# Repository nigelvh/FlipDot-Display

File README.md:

# FlipDot Display Driver
A driver for a flipdot display I found on eBay. Unfortunately I haven't found what the make/model of the display is. The design was based entirely on reverse engineering the connections.

## Hardware
These are the hardware design files. They're almost certainly terrible. Replicate this device at your own peril.

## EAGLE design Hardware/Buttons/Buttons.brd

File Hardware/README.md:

# Hardware Design
There are two custom PCBs I designed for this project, one simple one just supporting the input buttons, and the other that contains the actual logic and drivers for the flipdot panel.

The ESP32 handles all of the logic for the display, and feeds into the driver shift registers.

The drivers are MIC5841 (Low Side) and MIC5891 (High Side) devices, there's three pairs covering the 21 columns, and then two pairs covering the 14 rows. There are NAND gates on each set that provide an interlock preventing both the high side and low side drivers being active at the same time.

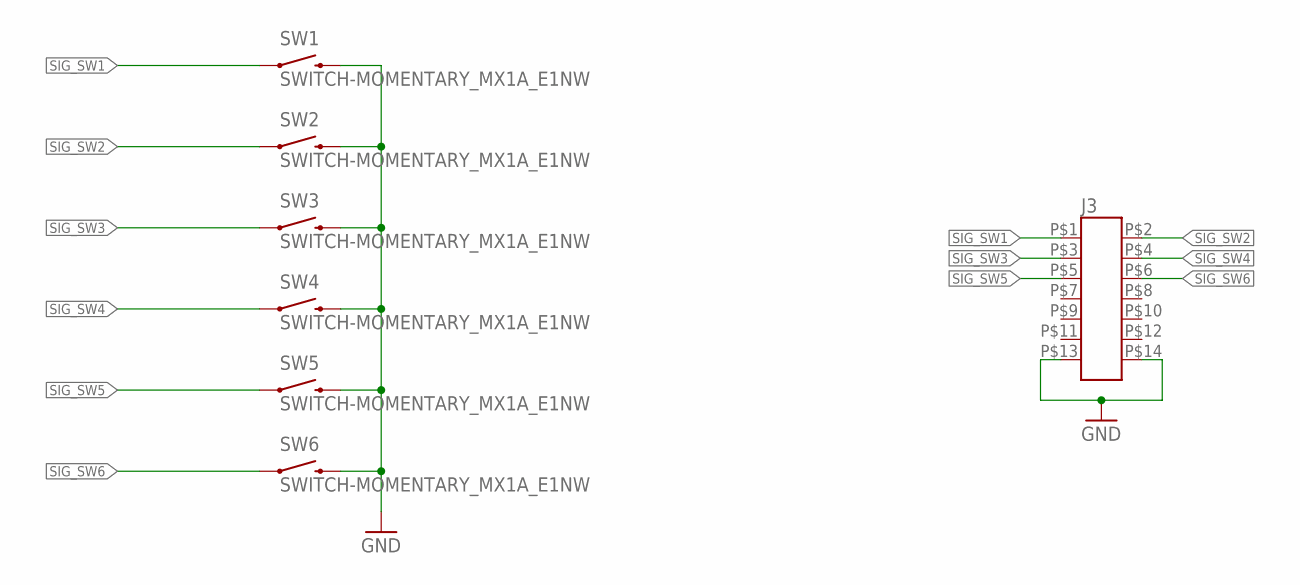
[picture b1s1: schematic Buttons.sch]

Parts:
J3: HEADER-2X7; 3M-3000SERIES-HEADER-RIGHTANGLE
SW1, SW2, SW3, SW4, SW5, SW6: SWITCH-MOMENTARY_MX1A_E1NW; CHERRY_MX1A_E1NW

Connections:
GND: J3.P$13 (13), J3.P$14 (14), SW1.P$2 (2), SW2.P$2 (2), SW3.P$2 (2), SW4.P$2 (2), SW5.P$2 (2), SW6.P$2 (2)
SIG_SW1: J3.P$1 (1), SW1.P$1 (1)
SIG_SW2: J3.P$2 (2), SW2.P$1 (1)
SIG_SW3: J3.P$3 (3), SW3.P$1 (1)
SIG_SW4: J3.P$4 (4), SW4.P$1 (1)
SIG_SW5: J3.P$5 (5), SW5.P$1 (1)
SIG_SW6: J3.P$6 (6), SW6.P$1 (1)

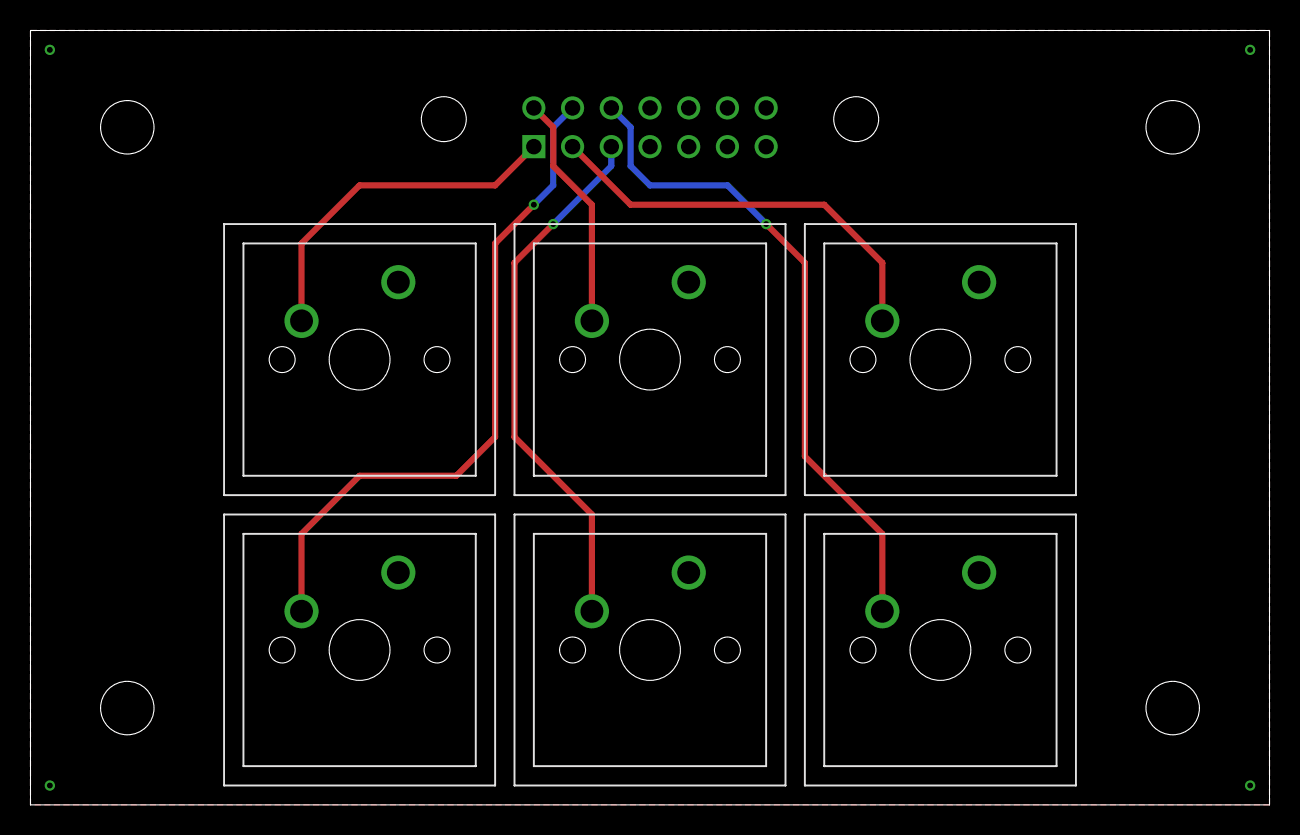
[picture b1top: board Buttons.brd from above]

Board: 2 copper layers, 81.3 x 50.8 mm, 7 parts (0 on the bottom side), 7 nets.

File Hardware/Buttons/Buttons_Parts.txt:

Partlist

Exported from Buttons.sch at 7/29/24 21:16

EAGLE Version 7.7.0 Copyright (c) 1988-2016 CadSoft

Assembly variant: 

Part     Value                      Device                     Package                         Library  Sheet

J3       HEADER-2X7                 HEADER-2X7                 3M-3000SERIES-HEADER-RIGHTANGLE Nigel    1
SW1      SWITCH-MOMENTARY_MX1A_E1NW SWITCH-MOMENTARY_MX1A_E1NW CHERRY_MX1A_E1NW                Nigel    1
SW2      SWITCH-MOMENTARY_MX1A_E1NW SWITCH-MOMENTARY_MX1A_E1NW CHERRY_MX1A_E1NW                Nigel    1
SW3      SWITCH-MOMENTARY_MX1A_E1NW SWITCH-MOMENTARY_MX1A_E1NW CHERRY_MX1A_E1NW                Nigel    1
SW4      SWITCH-MOMENTARY_MX1A_E1NW SWITCH-MOMENTARY_MX1A_E1NW CHERRY_MX1A_E1NW                Nigel    1
SW5      SWITCH-MOMENTARY_MX1A_E1NW SWITCH-MOMENTARY_MX1A_E1NW CHERRY_MX1A_E1NW                Nigel    1
SW6      SWITCH-MOMENTARY_MX1A_E1NW SWITCH-MOMENTARY_MX1A_E1NW CHERRY_MX1A_E1NW                Nigel    1

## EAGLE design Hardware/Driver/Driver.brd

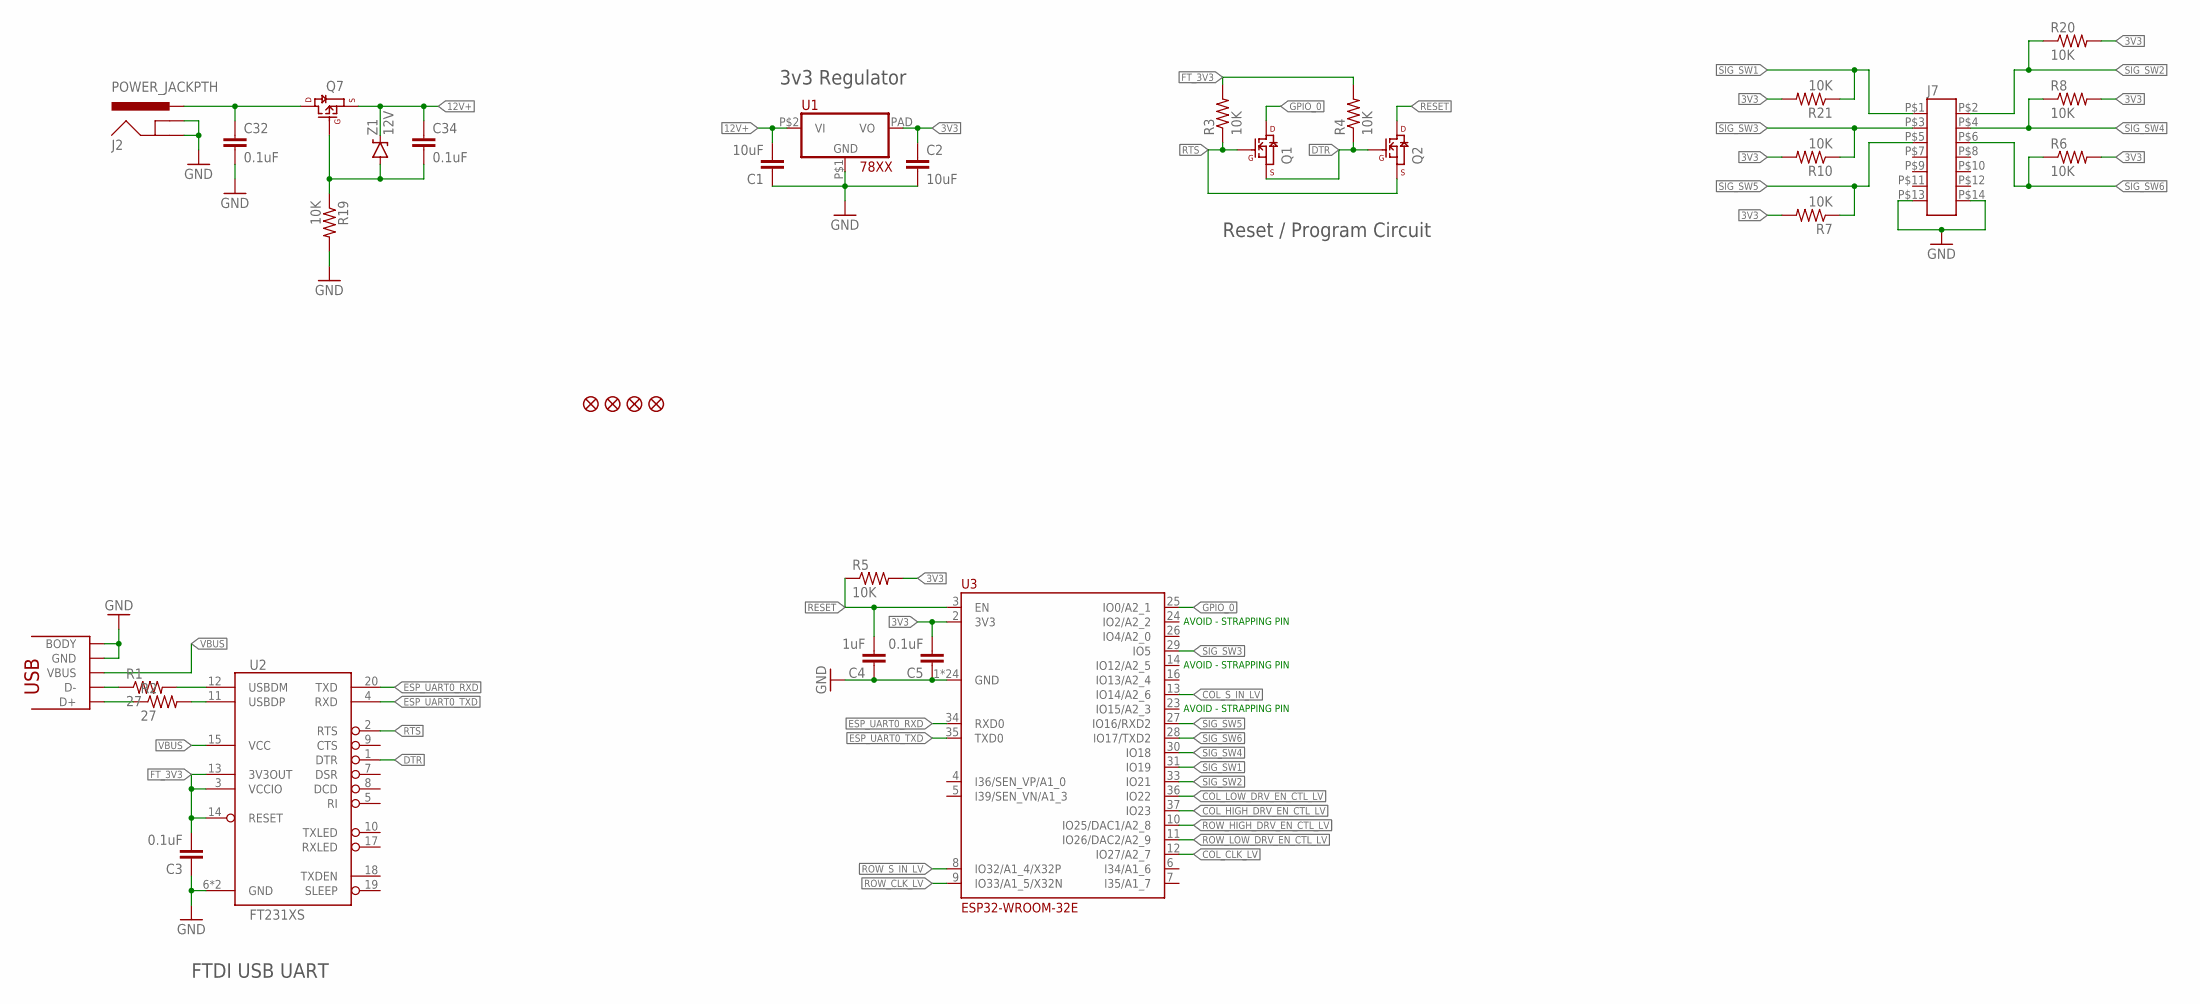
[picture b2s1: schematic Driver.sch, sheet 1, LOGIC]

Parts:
C1, C2: 10uF; 1206
C3, C5, C32, C34: 0.1uF; 0603-CAP
C4: 1uF; 0603-CAP
FID1, FID2, FID3, FID4: FIDUCIAL
J1: USB-MICROB; USB-MICROB-10118192
J2: POWER_JACKPTH; POWER_JACK_PTH
J7: HEADER-2X7; 3M-3000SERIES-HEADER-RIGHTANGLE
Q1, Q2: MOSFET_N_CHANNELFDV305N; SOT-23
Q7: MOSFET_P_CHANNELDMP4015SSS; SO08
R1, R2: 27; 0603-RES
R3, R4, R5, R6, R7, R8, R10, R19, R20, R21: 10K; 0603-RES
U1: 7805AZ1117_TO252; DPAK-3
U2: FT231XS; SSOP-20
U3: ESP32-WROOM-32E
Z1: 12V; SOT-23

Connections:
3V3: C2.1, C5.2, R5.2, R6.2, R7.2, R8.2, R10.2, R20.2, R21.2, U1.PAD (VO), U3.2 (3V3); also elsewhere on the board
12V+: C1.2, C34.1, Q7.1 (S), Q7.2 (S), Q7.3 (S), U1.P$2 (VI), Z1.3 (C); also elsewhere on the board
COL_CLK_LV: U3.12 (IO27/A2_7); also elsewhere on the board
COL_HIGH_DRV_EN_CTL_LV: U3.37 (IO23); also elsewhere on the board
COL_LOW_DRV_EN_CTL_LV: U3.36 (IO22); also elsewhere on the board
COL_S_IN_LV: U3.13 (IO14/A2_6); also elsewhere on the board
DTR: Q1.2 (S), Q2.1 (G), R4.1, U2.1 (DTR)
ESP_UART0_RXD: U2.20 (TXD), U3.34 (RXD0)
ESP_UART0_TXD: U2.4 (RXD), U3.35 (TXD0)
FT_3V3: C3.2, R3.2, R4.2, U2.3 (VCCIO), U2.13 (3V3OUT), U2.14 (RESET)
GND: C1.1, C2.2, C3.1, C4.1, C5.1, C32.2, J1.5 (GND), J1.BODY@1 (BODY), J1.BODY@2 (BODY), J1.BODY@3 (BODY), J1.BODY@4 (BODY), J1.BODY@5 (BODY), J1.BODY@6 (BODY), J2.GND, J2.GNDBREAK, J7.P$13 (13), J7.P$14 (14), R19.2, U1.P$1 (GND), U2.6 (GND), U2.16 (GND), U3.1 (GND), U3.15 (GND), U3.38 (GND), U3.P$1 (GND), U3.P$2 (GND), U3.P$3 (GND), U3.P$4 (GND), U3.P$5 (GND), U3.P$6 (GND), U3.P$7 (GND), U3.P$8 (GND), U3.P$9 (GND), U3.P$10 (GND), U3.P$11 (GND), U3.P$12 (GND), U3.PAD@1 (GND), U3.PAD@2 (GND), U3.PAD@3 (GND), U3.PAD@4 (GND), U3.PAD@5 (GND), U3.PAD@6 (GND), U3.PAD@7 (GND), U3.PAD@8 (GND), U3.PAD@9 (GND); also elsewhere on the board
GPIO_0: Q1.3 (D), U3.25 (IO0/A2_1)
unnamed: J1.2 (D-), R1.1
unnamed: J1.3 (D+), R2.1
unnamed: R2.2, U2.11 (USBDP)
unnamed: R1.2, U2.12 (USBDM)
unnamed: C32.1, J2.PWR, Q7.5 (D), Q7.6 (D), Q7.7 (D), Q7.8 (D)
unnamed: C34.2, Q7.4 (G), R19.1, Z1.1 (A)
RESET: C4.2, Q2.3 (D), R5.1, U3.3 (EN)
ROW_CLK_LV: U3.9 (IO33/A1_5/X32N); also elsewhere on the board
ROW_HIGH_DRV_EN_CTL_LV: U3.10 (IO25/DAC1/A2_8); also elsewhere on the board
ROW_LOW_DRV_EN_CTL_LV: U3.11 (IO26/DAC2/A2_9); also elsewhere on the board
ROW_S_IN_LV: U3.8 (IO32/A1_4/X32P); also elsewhere on the board
RTS: Q1.1 (G), Q2.2 (S), R3.1, U2.2 (RTS)
SIG_SW1: J7.P$1 (1), R21.1, U3.31 (IO19)
SIG_SW2: J7.P$2 (2), R20.1, U3.33 (IO21)
SIG_SW3: J7.P$3 (3), R10.1, U3.29 (IO5)
SIG_SW4: J7.P$4 (4), R8.1, U3.30 (IO18)
SIG_SW5: J7.P$5 (5), R7.1, U3.27 (IO16/RXD2)
SIG_SW6: J7.P$6 (6), R6.1, U3.28 (IO17/TXD2)
VBUS: J1.1 (VBUS), U2.15 (VCC)

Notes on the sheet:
FTDI USB UART
3v3 Regulator
Reset / Program Circuit
AVOID - STRAPPING PIN

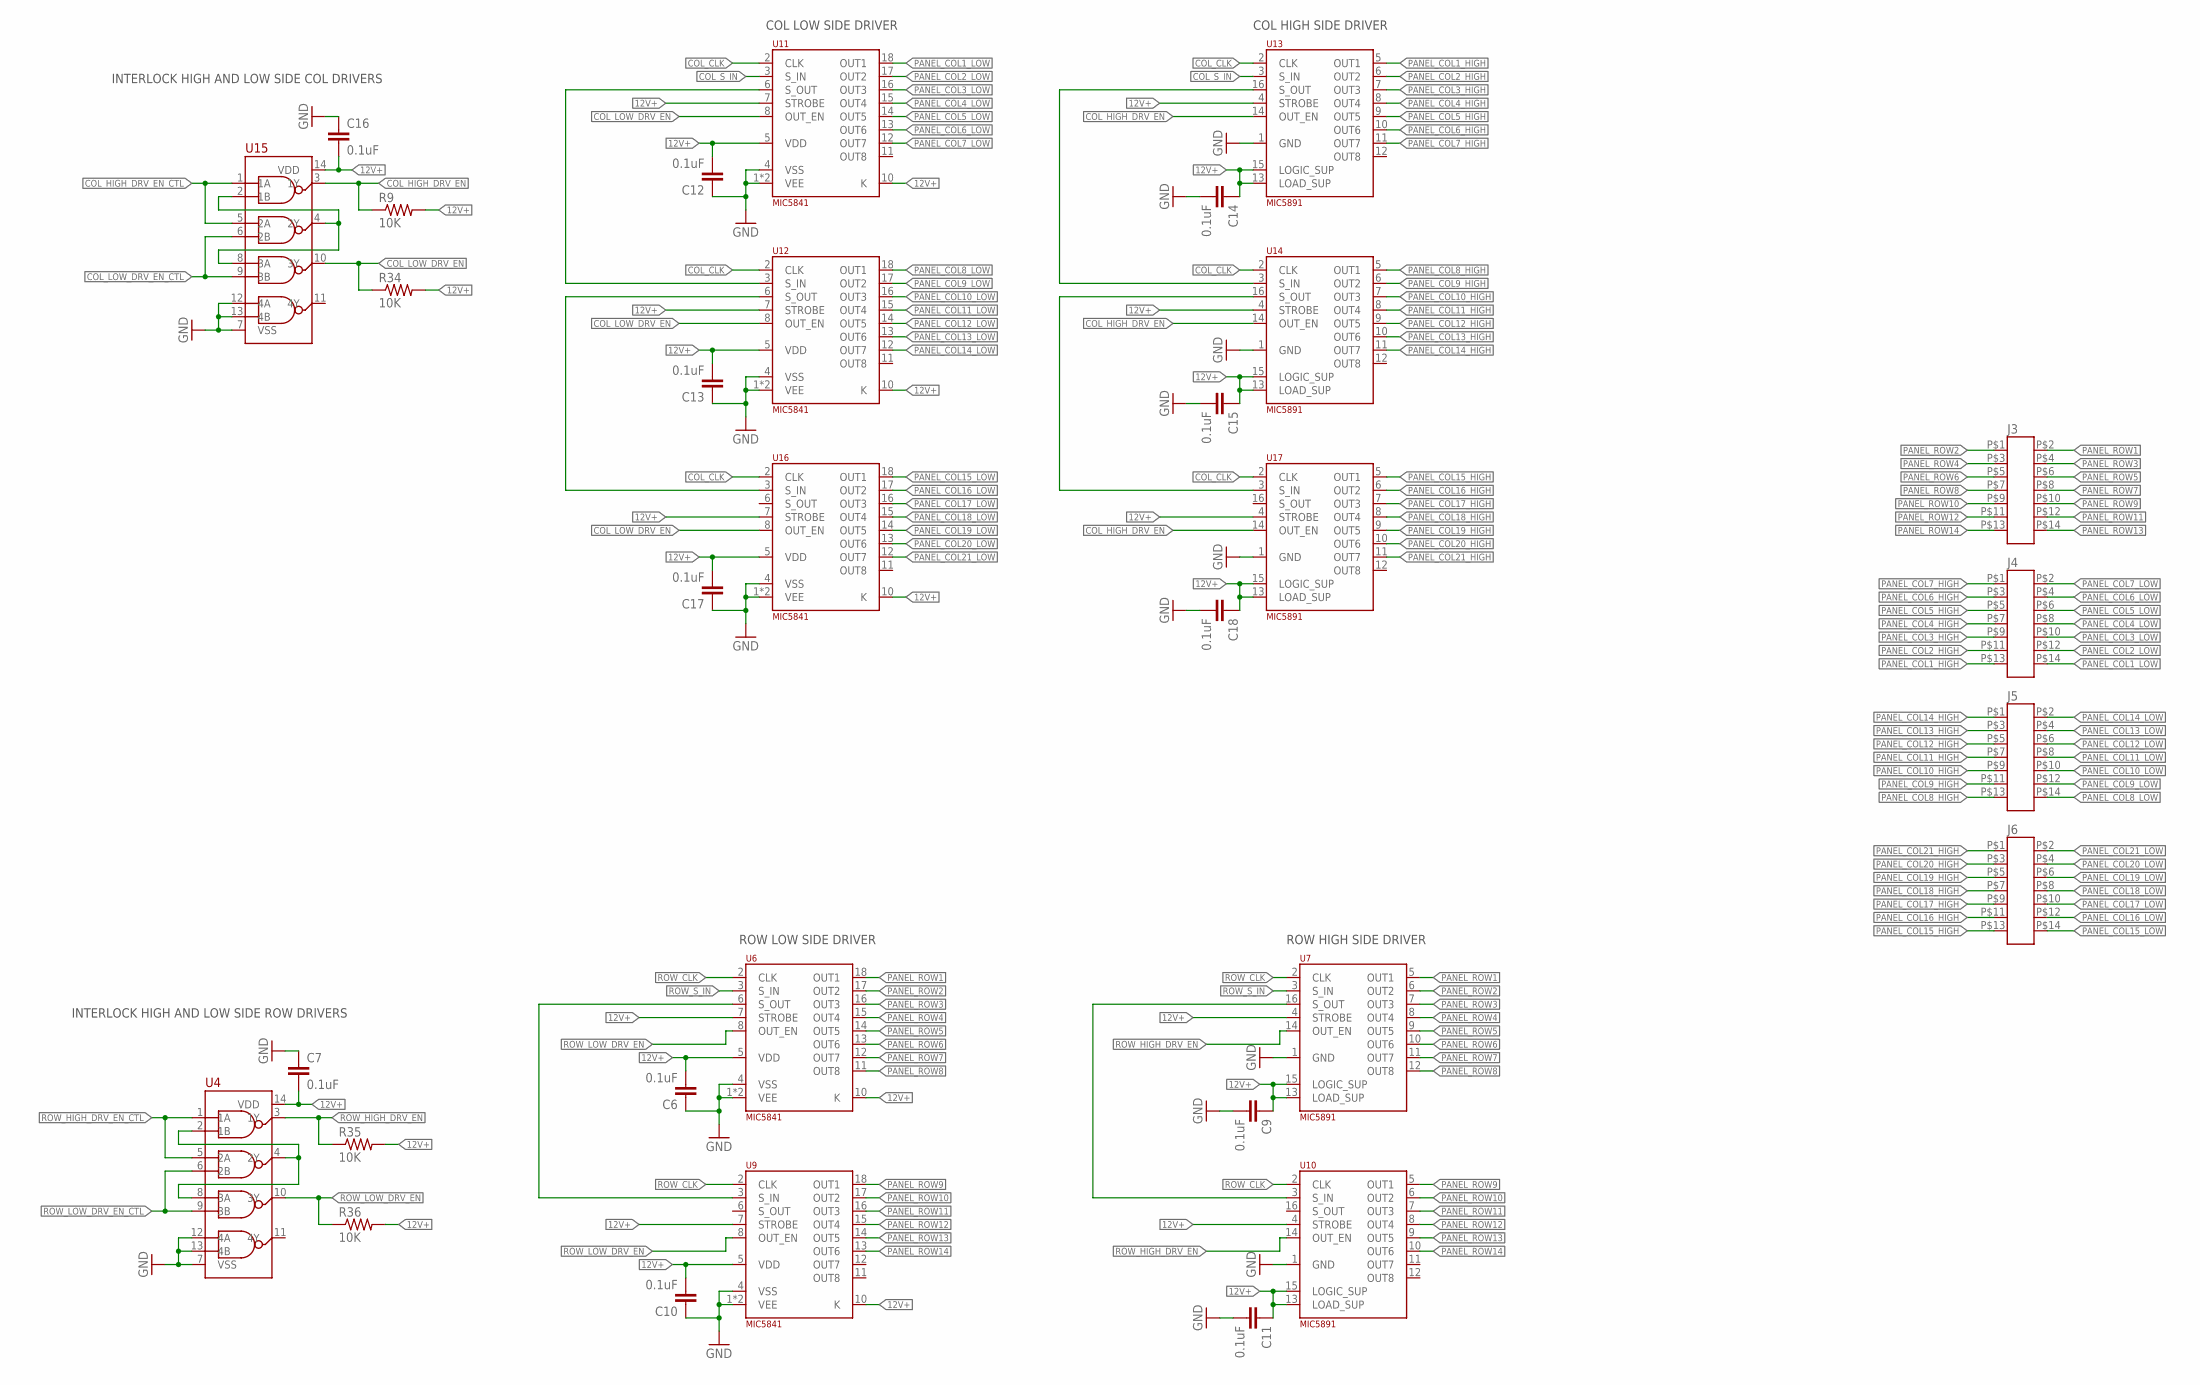
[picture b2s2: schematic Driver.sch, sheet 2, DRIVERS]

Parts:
C6, C7, C9, C10, C11, C12, C13, C14, C15, C16, C17, C18: 0.1uF; 0603-CAP
J3, J4, J5, J6: HEADER-2X7; 3M-3000SERIES-HEADER-RIGHTANGLE
R9, R34, R35, R36: 10K; 0603-RES
U4, U15: HEF4093B; SOIC-14
U6, U9, U11, U12, U16: MIC5841; SOIC-18-WIDE
U7, U10, U13, U14, U17: MIC5891; SOIC-16-WIDE

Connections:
12V+: C6.2, C7.2, C9.1, C10.2, C11.1, C12.2, C13.2, C14.1, C15.1, C16.2, C17.2, C18.1, R9.2, R34.2, R35.2, R36.2, U4.14 (VDD), U6.5 (VDD), U6.7 (STROBE), U6.10 (K), U7.4 (STROBE), U7.13 (LOAD_SUP), U7.15 (LOGIC_SUP), U9.5 (VDD), U9.7 (STROBE), U9.10 (K), U10.4 (STROBE), U10.13 (LOAD_SUP), U10.15 (LOGIC_SUP), U11.5 (VDD), U11.7 (STROBE), U11.10 (K), U12.5 (VDD), U12.7 (STROBE), U12.10 (K), U13.4 (STROBE), U13.13 (LOAD_SUP), U13.15 (LOGIC_SUP), U14.4 (STROBE), U14.13 (LOAD_SUP), U14.15 (LOGIC_SUP), U15.14 (VDD), U16.5 (VDD), U16.7 (STROBE), U16.10 (K), U17.4 (STROBE), U17.13 (LOAD_SUP), U17.15 (LOGIC_SUP); also elsewhere on the board
COL_CLK: U11.2 (CLK), U12.2 (CLK), U13.2 (CLK), U14.2 (CLK), U16.2 (CLK), U17.2 (CLK); also elsewhere on the board
COL_HIGH_DRV_EN: R9.1, U13.14 (OUT_EN), U14.14 (OUT_EN), U15.3 (1Y), U17.14 (OUT_EN)
COL_HIGH_DRV_EN_CTL: U15.1 (1A), U15.5 (2A); also elsewhere on the board
COL_LOW_DRV_EN: R34.1, U11.8 (OUT_EN), U12.8 (OUT_EN), U15.10 (3Y), U16.8 (OUT_EN)
COL_LOW_DRV_EN_CTL: U15.6 (2B), U15.9 (3B); also elsewhere on the board
COL_S_IN: U11.3 (S_IN), U13.3 (S_IN); also elsewhere on the board
GND: C6.1, C7.1, C9.2, C10.1, C11.2, C12.1, C13.1, C14.2, C15.2, C16.1, C17.1, C18.2, U4.7 (VSS), U4.12 (4A), U4.13 (4B), U6.1 (VEE), U6.4 (VSS), U6.9 (VEE), U7.1 (GND), U9.1 (VEE), U9.4 (VSS), U9.9 (VEE), U10.1 (GND), U11.1 (VEE), U11.4 (VSS), U11.9 (VEE), U12.1 (VEE), U12.4 (VSS), U12.9 (VEE), U13.1 (GND), U14.1 (GND), U15.7 (VSS), U15.12 (4A), U15.13 (4B), U16.1 (VEE), U16.4 (VSS), U16.9 (VEE), U17.1 (GND); also elsewhere on the board
unnamed: U6.6 (S_OUT), U9.3 (S_IN)
unnamed: U4.2 (1B), U4.4 (2Y), U4.8 (3A)
unnamed: U7.16 (S_OUT), U10.3 (S_IN)
unnamed: U11.6 (S_OUT), U12.3 (S_IN)
unnamed: U13.16 (S_OUT), U14.3 (S_IN)
unnamed: U15.2 (1B), U15.4 (2Y), U15.8 (3A)
unnamed: U12.6 (S_OUT), U16.3 (S_IN)
unnamed: U14.16 (S_OUT), U17.3 (S_IN)
PANEL_COL1_HIGH: J4.P$13 (13), U13.5 (OUT1)
PANEL_COL1_LOW: J4.P$14 (14), U11.18 (OUT1)
PANEL_COL2_HIGH: J4.P$11 (11), U13.6 (OUT2)
PANEL_COL2_LOW: J4.P$12 (12), U11.17 (OUT2)
PANEL_COL3_HIGH: J4.P$9 (9), U13.7 (OUT3)
PANEL_COL3_LOW: J4.P$10 (10), U11.16 (OUT3)
PANEL_COL4_HIGH: J4.P$7 (7), U13.8 (OUT4)
PANEL_COL4_LOW: J4.P$8 (8), U11.15 (OUT4)
PANEL_COL5_HIGH: J4.P$5 (5), U13.9 (OUT5)
PANEL_COL5_LOW: J4.P$6 (6), U11.14 (OUT5)
PANEL_COL6_HIGH: J4.P$3 (3), U13.10 (OUT6)
PANEL_COL6_LOW: J4.P$4 (4), U11.13 (OUT6)
PANEL_COL7_HIGH: J4.P$1 (1), U13.11 (OUT7)
PANEL_COL7_LOW: J4.P$2 (2), U11.12 (OUT7)
PANEL_COL8_HIGH: J5.P$13 (13), U14.5 (OUT1)
PANEL_COL8_LOW: J5.P$14 (14), U12.18 (OUT1)
PANEL_COL9_HIGH: J5.P$11 (11), U14.6 (OUT2)
PANEL_COL9_LOW: J5.P$12 (12), U12.17 (OUT2)
PANEL_COL10_HIGH: J5.P$9 (9), U14.7 (OUT3)
PANEL_COL10_LOW: J5.P$10 (10), U12.16 (OUT3)
PANEL_COL11_HIGH: J5.P$7 (7), U14.8 (OUT4)
PANEL_COL11_LOW: J5.P$8 (8), U12.15 (OUT4)
PANEL_COL12_HIGH: J5.P$5 (5), U14.9 (OUT5)
PANEL_COL12_LOW: J5.P$6 (6), U12.14 (OUT5)
PANEL_COL13_HIGH: J5.P$3 (3), U14.10 (OUT6)
PANEL_COL13_LOW: J5.P$4 (4), U12.13 (OUT6)
PANEL_COL14_HIGH: J5.P$1 (1), U14.11 (OUT7)
PANEL_COL14_LOW: J5.P$2 (2), U12.12 (OUT7)
PANEL_COL15_HIGH: J6.P$13 (13), U17.5 (OUT1)
PANEL_COL15_LOW: J6.P$14 (14), U16.18 (OUT1)
PANEL_COL16_HIGH: J6.P$11 (11), U17.6 (OUT2)
PANEL_COL16_LOW: J6.P$12 (12), U16.17 (OUT2)
PANEL_COL17_HIGH: J6.P$9 (9), U17.7 (OUT3)
PANEL_COL17_LOW: J6.P$10 (10), U16.16 (OUT3)
PANEL_COL18_HIGH: J6.P$7 (7), U17.8 (OUT4)
PANEL_COL18_LOW: J6.P$8 (8), U16.15 (OUT4)
PANEL_COL19_HIGH: J6.P$5 (5), U17.9 (OUT5)
PANEL_COL19_LOW: J6.P$6 (6), U16.14 (OUT5)
PANEL_COL20_HIGH: J6.P$3 (3), U17.10 (OUT6)
PANEL_COL20_LOW: J6.P$4 (4), U16.13 (OUT6)
PANEL_COL21_HIGH: J6.P$1 (1), U17.11 (OUT7)
PANEL_COL21_LOW: J6.P$2 (2), U16.12 (OUT7)
PANEL_ROW1: J3.P$2 (2), U6.18 (OUT1), U7.5 (OUT1)
PANEL_ROW2: J3.P$1 (1), U6.17 (OUT2), U7.6 (OUT2)
PANEL_ROW3: J3.P$4 (4), U6.16 (OUT3), U7.7 (OUT3)
PANEL_ROW4: J3.P$3 (3), U6.15 (OUT4), U7.8 (OUT4)
PANEL_ROW5: J3.P$6 (6), U6.14 (OUT5), U7.9 (OUT5)
PANEL_ROW6: J3.P$5 (5), U6.13 (OUT6), U7.10 (OUT6)
PANEL_ROW7: J3.P$8 (8), U6.12 (OUT7), U7.11 (OUT7)
PANEL_ROW8: J3.P$7 (7), U6.11 (OUT8), U7.12 (OUT8)
PANEL_ROW9: J3.P$10 (10), U9.18 (OUT1), U10.5 (OUT1)
PANEL_ROW10: J3.P$9 (9), U9.17 (OUT2), U10.6 (OUT2)
PANEL_ROW11: J3.P$12 (12), U9.16 (OUT3), U10.7 (OUT3)
PANEL_ROW12: J3.P$11 (11), U9.15 (OUT4), U10.8 (OUT4)
PANEL_ROW13: J3.P$14 (14), U9.14 (OUT5), U10.9 (OUT5)
PANEL_ROW14: J3.P$13 (13), U9.13 (OUT6), U10.10 (OUT6)
ROW_CLK: U6.2 (CLK), U7.2 (CLK), U9.2 (CLK), U10.2 (CLK); also elsewhere on the board
ROW_HIGH_DRV_EN: R35.1, U4.3 (1Y), U7.14 (OUT_EN), U10.14 (OUT_EN)
ROW_HIGH_DRV_EN_CTL: U4.1 (1A), U4.5 (2A); also elsewhere on the board
ROW_LOW_DRV_EN: R36.1, U4.10 (3Y), U6.8 (OUT_EN), U9.8 (OUT_EN)
ROW_LOW_DRV_EN_CTL: U4.6 (2B), U4.9 (3B); also elsewhere on the board
ROW_S_IN: U6.3 (S_IN), U7.3 (S_IN); also elsewhere on the board

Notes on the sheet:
INTERLOCK HIGH AND LOW SIDE ROW DRIVERS
ROW LOW SIDE DRIVER
ROW HIGH SIDE DRIVER
COL LOW SIDE DRIVER
COL HIGH SIDE DRIVER
INTERLOCK HIGH AND LOW SIDE COL DRIVERS

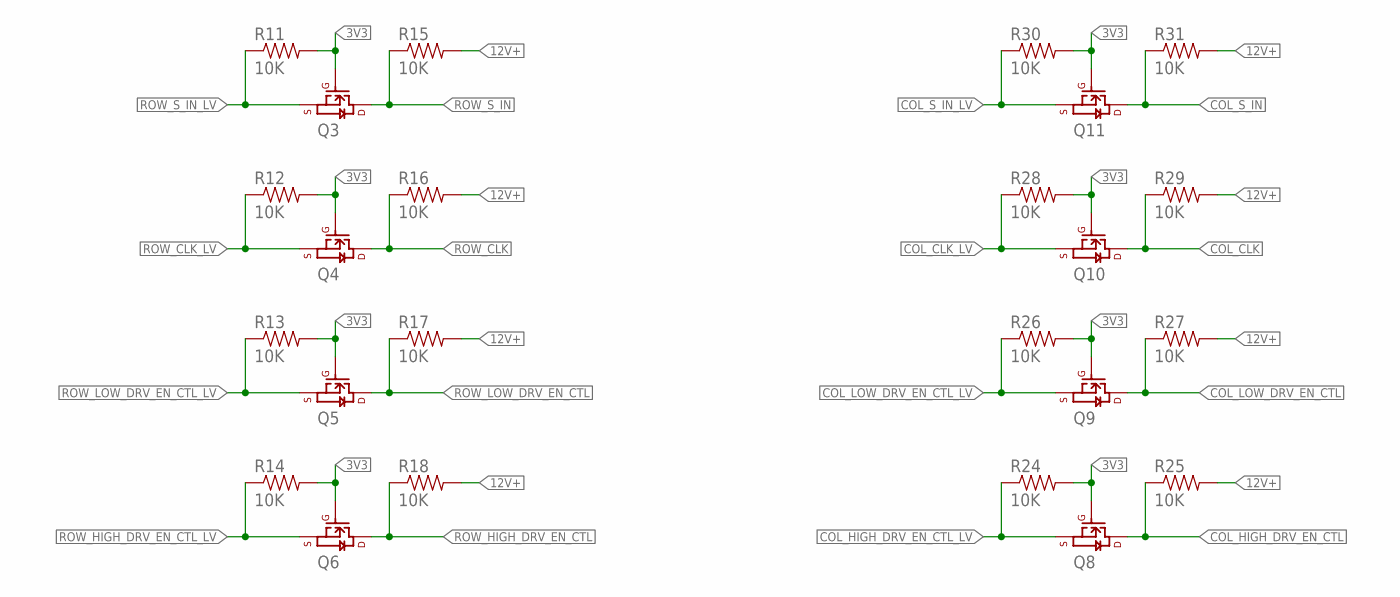
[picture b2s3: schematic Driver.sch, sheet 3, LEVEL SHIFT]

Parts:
Q3, Q4, Q5, Q6, Q8, Q9, Q10, Q11: MOSFET_N_CHANNELFDV305N; SOT-23
R11, R12, R13, R14, R15, R16, R17, R18, R24, R25, R26, R27, R28, R29, R30, R31: 10K; 0603-RES

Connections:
3V3: Q3.1 (G), Q4.1 (G), Q5.1 (G), Q6.1 (G), Q8.1 (G), Q9.1 (G), Q10.1 (G), Q11.1 (G), R11.2, R12.2, R13.2, R14.2, R24.2, R26.2, R28.2, R30.2; also elsewhere on the board
12V+: R15.2, R16.2, R17.2, R18.2, R25.2, R27.2, R29.2, R31.2; also elsewhere on the board
COL_CLK: Q10.3 (D), R29.1; also elsewhere on the board
COL_CLK_LV: Q10.2 (S), R28.1; also elsewhere on the board
COL_HIGH_DRV_EN_CTL: Q8.3 (D), R25.1; also elsewhere on the board
COL_HIGH_DRV_EN_CTL_LV: Q8.2 (S), R24.1; also elsewhere on the board
COL_LOW_DRV_EN_CTL: Q9.3 (D), R27.1; also elsewhere on the board
COL_LOW_DRV_EN_CTL_LV: Q9.2 (S), R26.1; also elsewhere on the board
COL_S_IN: Q11.3 (D), R31.1; also elsewhere on the board
COL_S_IN_LV: Q11.2 (S), R30.1; also elsewhere on the board
ROW_CLK: Q4.3 (D), R16.1; also elsewhere on the board
ROW_CLK_LV: Q4.2 (S), R12.1; also elsewhere on the board
ROW_HIGH_DRV_EN_CTL: Q6.3 (D), R18.1; also elsewhere on the board
ROW_HIGH_DRV_EN_CTL_LV: Q6.2 (S), R14.1; also elsewhere on the board
ROW_LOW_DRV_EN_CTL: Q5.3 (D), R17.1; also elsewhere on the board
ROW_LOW_DRV_EN_CTL_LV: Q5.2 (S), R13.1; also elsewhere on the board
ROW_S_IN: Q3.3 (D), R15.1; also elsewhere on the board
ROW_S_IN_LV: Q3.2 (S), R11.1; also elsewhere on the board

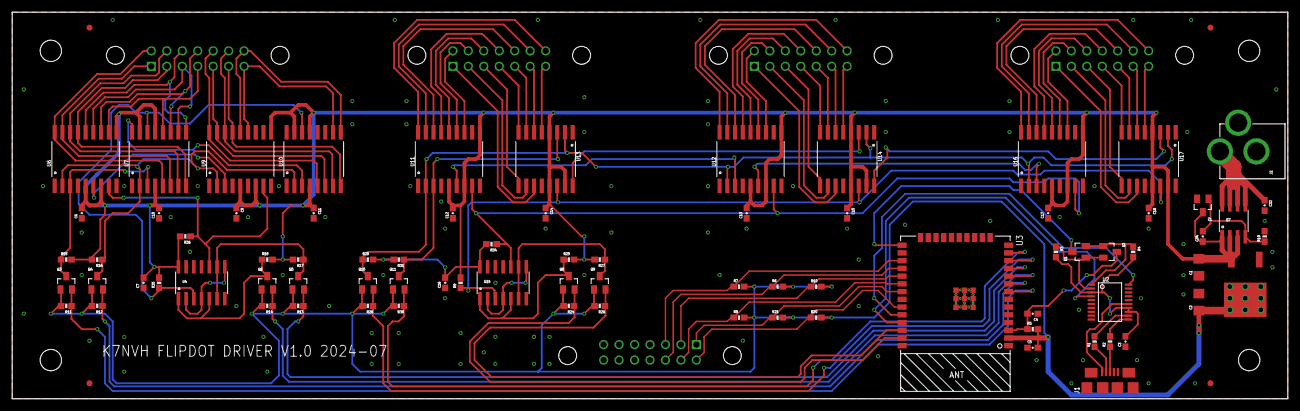
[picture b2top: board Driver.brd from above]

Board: 2 copper layers, 209.6 x 63.5 mm, 89 parts (0 on the bottom side), 107 nets.

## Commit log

2026-05-04 Added image to readme
2026-05-04 Added hardware design files

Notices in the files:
parts and their libraries:
SparkFun: Licensing: CC v3.0 Share-Alike You are welcome to use this library for commercial purposes.
